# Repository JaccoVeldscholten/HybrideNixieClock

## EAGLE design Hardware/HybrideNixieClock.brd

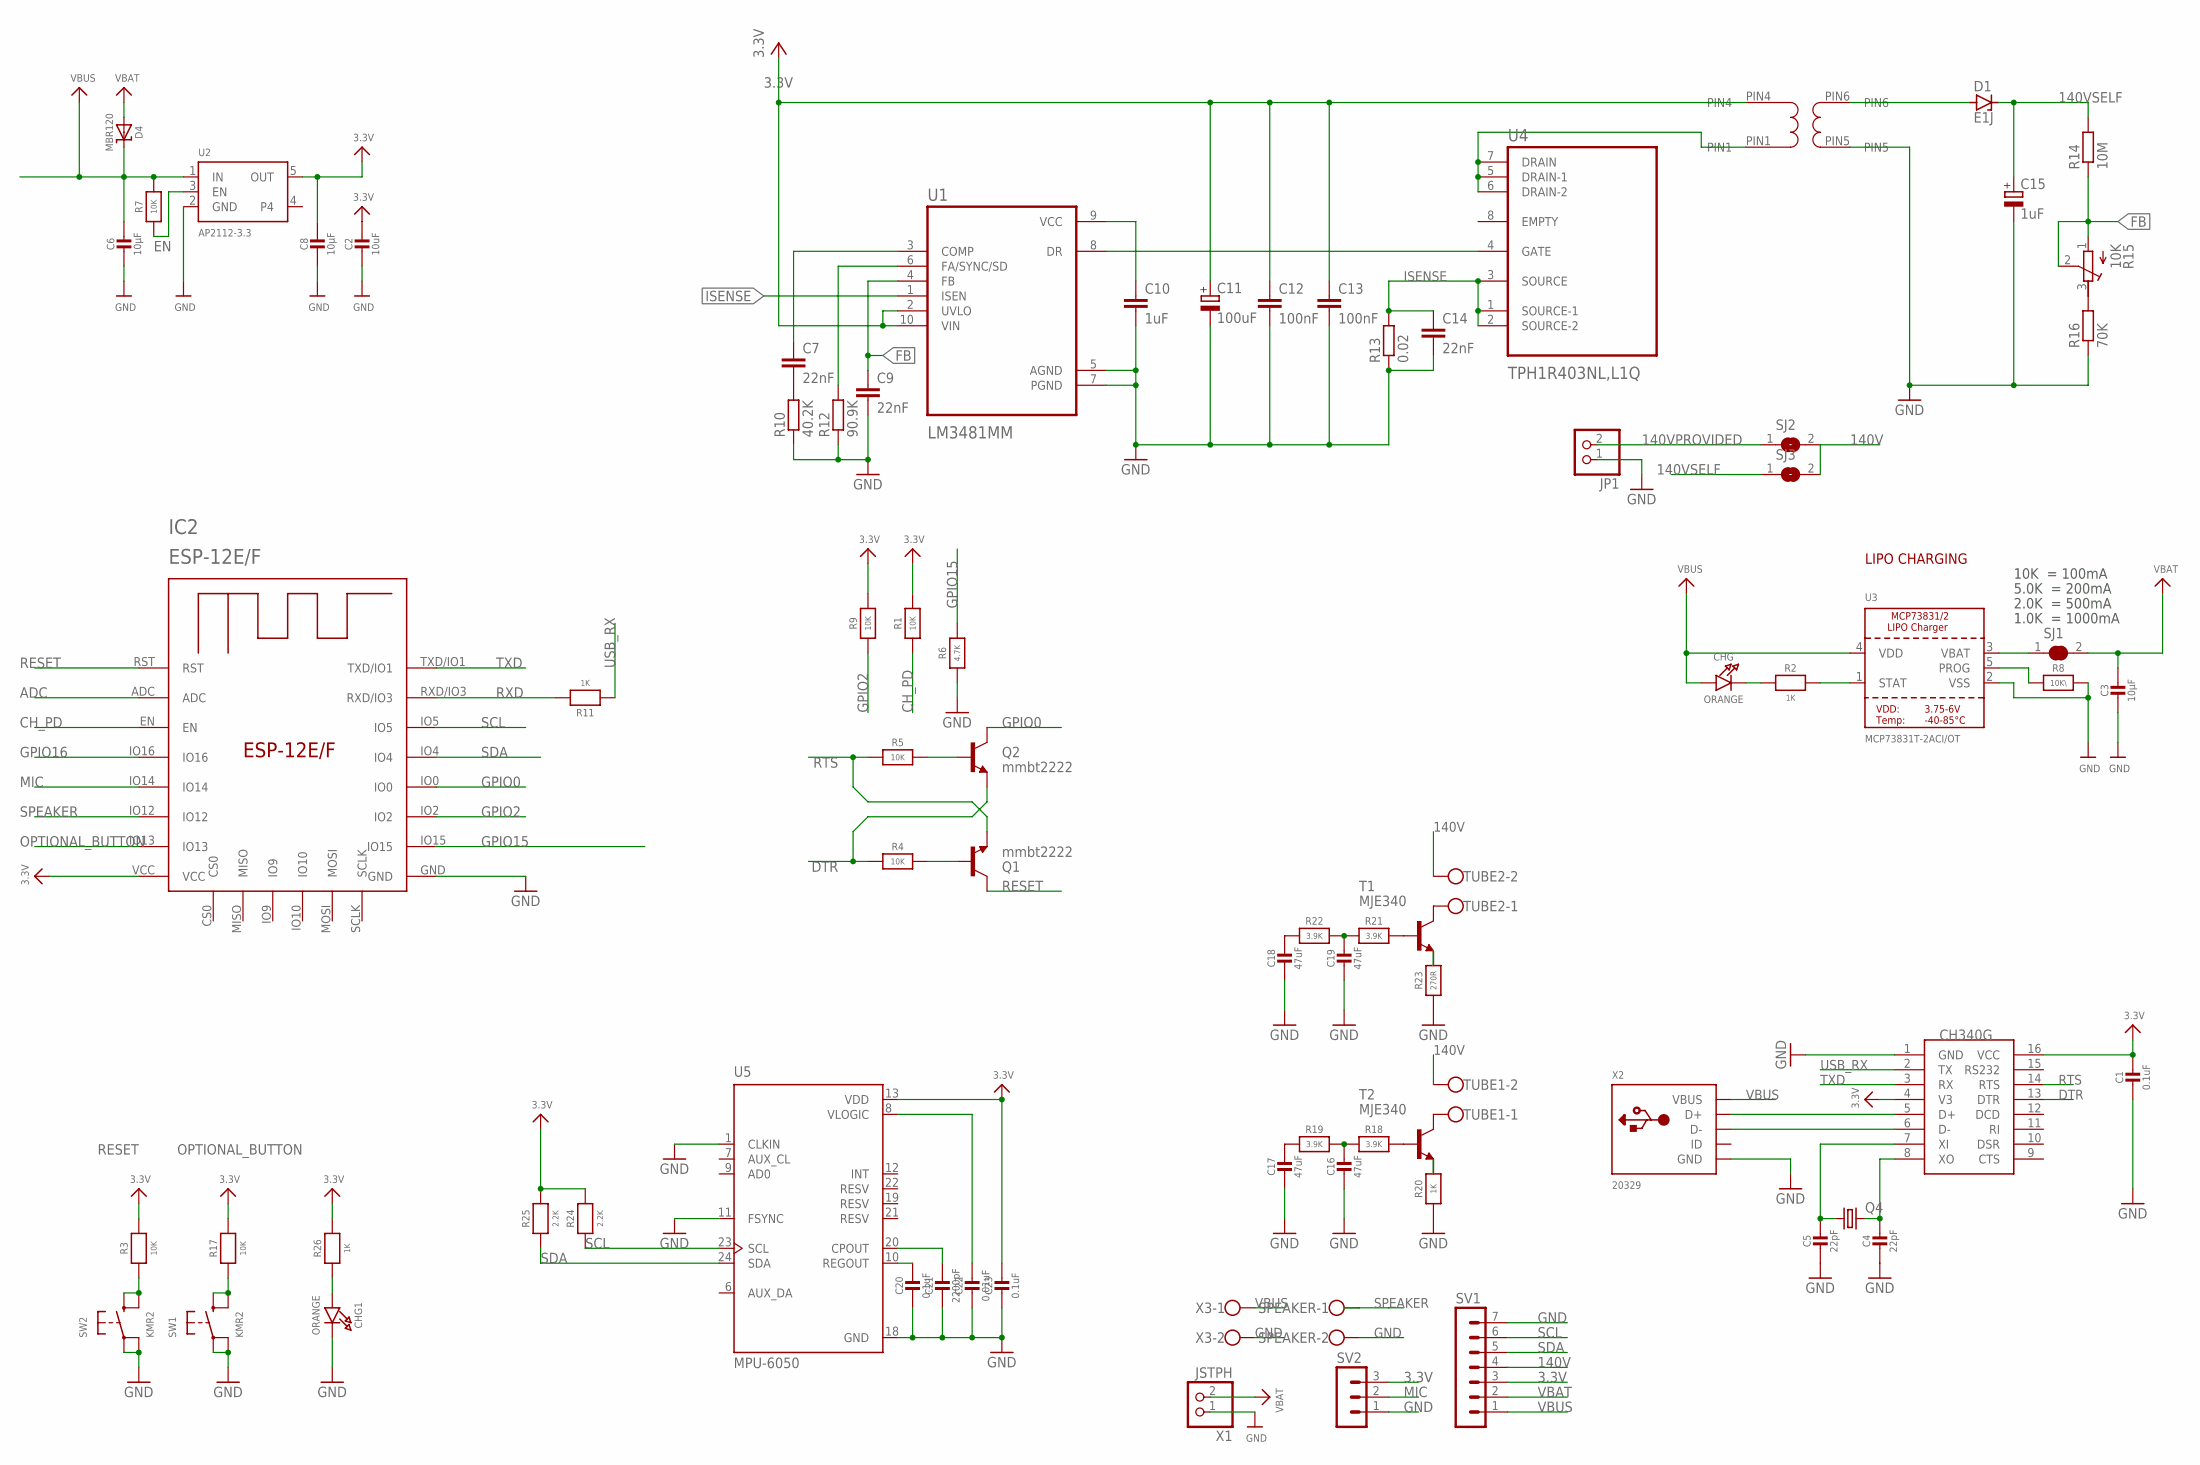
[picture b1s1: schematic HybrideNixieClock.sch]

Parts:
C1, C20, C23: 0.1uF; 0603-NO
C2: 10uF; 0805-NO
C3, C6, C8: 10µF; 0805-NO
C4, C5: 22pF; 0603-NO
C7, C9, C14: 22nF; C0603
C10: 1uF; C0603
C11: 100uF; CT3216
C12, C13: 100nF; C0603
C15: 1uF; CT3216
C16, C17, C18, C19: 47uF; 0603-NO
C21: 2200pF; 0603-NO
C22: 0.01uF; 0603-NO
CHG, CHG1: ORANGE; CHIPLED_0805_NOOUTLINE
D1: E1J; SMB
D4: MBR120; SOD-123
IC2: ESP-12E/F; ESP-12E
JP1: PINHD-1X2; 1X02
Q1, Q2: mmbt2222; SOT23-3
Q4: CRYSTALCTS406; CTS406
R1, R3, R4, R5, R7, R9, R17: 10K; 0603-NO
R2, R20, R26: 1K; 0603-NO
R6: 4.7K; 0603-NO
R8: 10K\; 0603-NO
R10: 40.2K; R0603
R11: 1K; _0603MP
R12: 90.9K; R0603
R13: 0.02; R0603
R14: 10M; R0603
R15: 10K; RTRIM4G/J
R16: 70K; R0603
R18, R19, R21, R22: 3.9K; 0603-NO
R23: 270R; 0603-NO
R24, R25: 2.2K; 0603-NO
SJ1: SOLDERJUMPER_CLOSED; SOLDERJUMPER_CLOSEDWIRE
SJ2, SJ3: SJ
SPEAKER: W237-102
SV1: MA07-1
SV2: MA03-1
SW1, SW2: KMR2; BTN_KMR2_4.6X2.8
T1, T2: MJE340; TO126
TUBE1, TUBE2: W237-102
U1: LM3481MM; SOP50P490X110-10N
U2: AP2112-3.3; SOT23-5
U3: MCP73831T-2ACI/OT; SOT23-5
U4: TPH1R403NL,L1Q; TRANS_TPHR8504PL,L1Q
U5: MPU-6050; QFN50P400X400X95-24N
U$6: TTRN-060S-013
U$7: CH340G; SOIC16
X1: JSTPH; JSTPH2
X2: 20329; 4UCONN_20329_V2
X3: W237-102

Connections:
3.3V: C1.1, C2.1, C8.1, C11.+, C12.1, C13.1, C23.1, IC2.VCC, R1.2, R3.2, R9.2, R17.2, R24.2, R25.2, R26.2, SV1.3, SV2.3, U1.2 (UVLO), U1.10 (VIN), U2.5 (OUT), U5.13 (VDD), U$6.PIN4, U$7.4 (V3), U$7.16 (VCC)
140V: SJ2.2, SJ3.2, SV1.4, TUBE1.2, TUBE2.2
140VPROVIDED: JP1.2, SJ2.1
140VSELF: C15.+, D1.C, R14.2, SJ3.1
ADC: IC2.ADC
CH_PD: IC2.EN, R1.1
DTR: Q2.2 (E), R4.1, U$7.13 (DTR)
EN: R7.1, U2.3 (EN)
FB: C9.1, R14.1, R15.1 (A), R15.2 (S), U1.4 (FB)
GND: C1.2, C2.2, C3.2, C4.2, C5.2, C6.2, C8.2, C9.2, C10.2, C11.-, C12.2, C13.2, C14.2, C15.-, C16.2, C17.2, C18.2, C19.2, C20.2, C21.2, C22.2, C23.2, CHG1.C, IC2.GND, JP1.1, R6.1, R8.2, R10.1, R12.1, R13.1, R16.1, R20.1, R23.1, SPEAKER.2, SV1.7, SV2.1, SW1.A, SW1.A' (P1), SW2.A, SW2.A' (P1), U1.5 (AGND), U1.7 (PGND), U2.2 (GND), U3.2 (VSS), U5.1 (CLKIN), U5.11 (FSYNC), U5.18 (GND), U$6.PIN5, U$7.1 (GND), X1.1, X2.BASE@1 (GND), X2.BASE@2 (GND), X2.GND, X2.SPRT@1 (GND), X2.SPRT@2 (GND), X2.SPRT@3 (GND), X2.SPRT@4 (GND), X3.2
GPIO0: IC2.IO0, Q2.3 (C)
GPIO2: IC2.IO2, R9.1
GPIO15: IC2.IO15, R6.2
GPIO16: IC2.IO16
ISENSE: C14.1, R13.2, U1.1 (ISEN), U4.1 (SOURCE-1), U4.2 (SOURCE-2), U4.3 (SOURCE)
MIC: IC2.IO14, SV2.2
unnamed: CHG.C, R2.1
unnamed: C7.2, R10.2
unnamed: R2.2, U3.1 (STAT)
unnamed: R8.1, U3.5 (PROG)
unnamed: C7.1, U1.3 (COMP)
unnamed: U4.5 (DRAIN-1), U4.6 (DRAIN-2), U4.7 (DRAIN), U$6.PIN1
unnamed: SJ1.1, U3.3 (VBAT)
unnamed: R18.2, T2.3 (B)
unnamed: U$7.6 (D-), X2.D-
unnamed: U$7.5 (D+), X2.D+
unnamed: D1.A, U1.8 (DR), U4.4 (GATE), U$6.PIN6
unnamed: Q1.1 (B), R4.2
unnamed: Q2.1 (B), R5.2
unnamed: C5.1, Q4.1, U$7.7 (XI)
unnamed: C4.1, Q4.3 (2), U$7.8 (XO)
unnamed: C10.1, U1.9 (VCC)
unnamed: R12.2, U1.6 (FA/SYNC/SD)
unnamed: R23.2, T1.1 (E)
unnamed: R15.3 (E), R16.2
unnamed: C16.1, R18.1, R19.2
unnamed: C17.1, R19.1
unnamed: R21.2, T1.3 (B)
unnamed: C19.1, R21.1, R22.2
unnamed: C18.1, R22.1
unnamed: T2.2 (C), TUBE1.1
unnamed: T1.2 (C), TUBE2.1
unnamed: R20.2, T2.1 (E)
unnamed: C20.1, U5.10 (REGOUT)
unnamed: C21.1, U5.20 (CPOUT)
unnamed: CHG1.A, R26.1
unnamed: C22.1, U5.8 (VLOGIC)
OPTIONAL_BUTTON: IC2.IO13, R17.1, SW1.B (S), SW1.B' (S1)
RESET: IC2.RST, Q1.3 (C), R3.1, SW2.B (S), SW2.B' (S1)
RTS: Q1.2 (E), R5.1, U$7.14 (RTS)
RXD: IC2.RXD/IO3, R11.2
SCL: IC2.IO5, R24.1, SV1.6, U5.23 (SCL)
SDA: IC2.IO4, R25.1, SV1.5, U5.24 (SDA)
SPEAKER: IC2.IO12, SPEAKER.1
TXD: IC2.TXD/IO1, U$7.3 (RX)
USB_RX: R11.1, U$7.2 (TX)
VBAT: C3.1, D4.A, SJ1.2, SV1.2, X1.2
VBUS: C6.1, CHG.A, D4.C, R7.2, SV1.1, U2.1 (IN), U3.4 (VDD), X2.VBUS, X3.1

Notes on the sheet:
10K = 100mA
5.0K = 200mA
2.0K = 500mA
1.0K = 1000mA
LIPO CHARGING

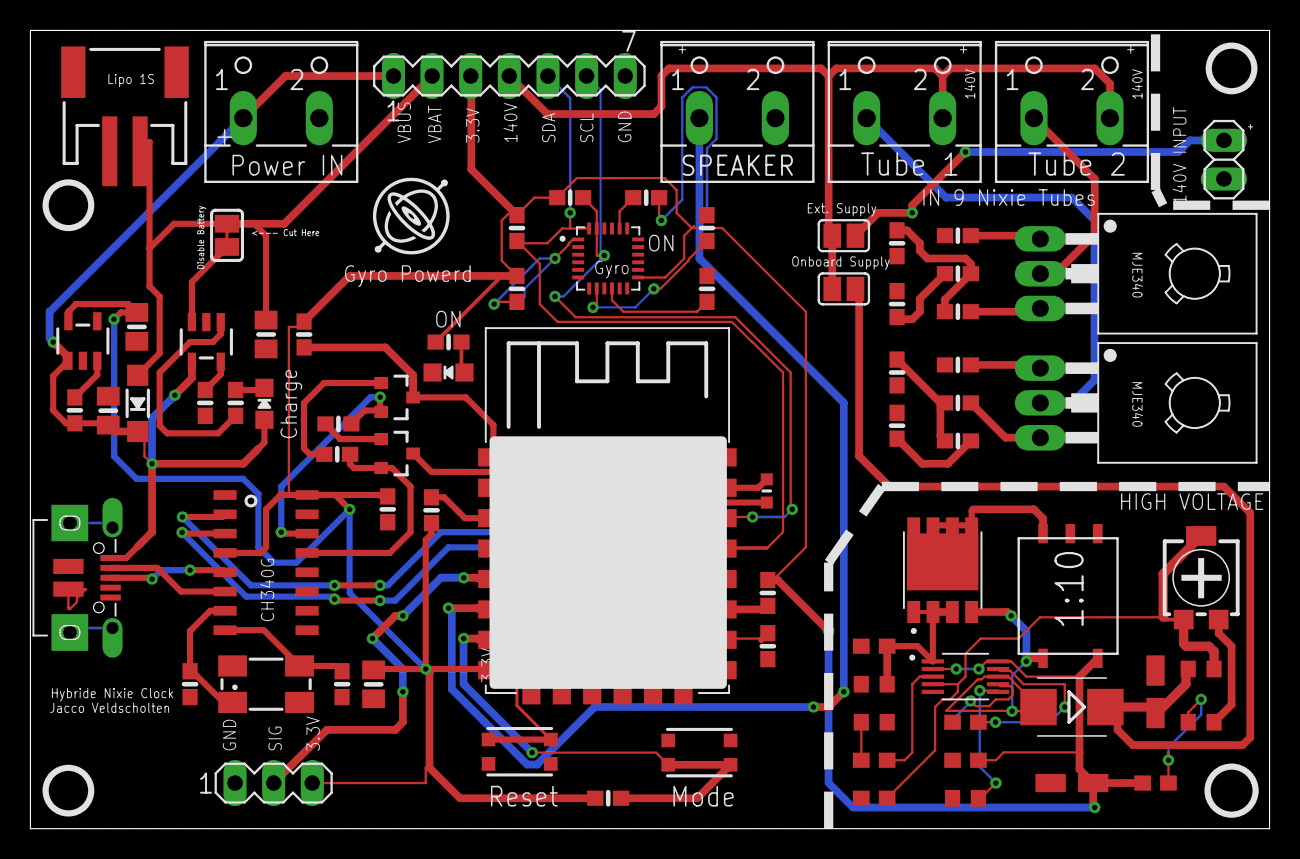
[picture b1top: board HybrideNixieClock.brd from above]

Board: 2 copper layers, 81.5 x 52.5 mm, 80 parts (0 on the bottom side), 56 nets.

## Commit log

2020-09-21 Added Schematic
2020-09-21 Create Schematic
2020-09-21 Moved Hardware to Folder
2020-09-22 Final V1 Hardware
2020-10-19 Updated Hardware V2
2020-12-07 Initial Master
2020-12-07 First setup. Connecting WifiManager + TimeManager
    First steps taken
    - Setting up UDP time
    - Working Gyro
    - Working WiFi Manager
    ToDo: Working Web Page to config the clock
2020-12-27 Initial Release webpage

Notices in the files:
parts and their libraries:
microbuilder: This work is placed in the public domain, and may be freely used for commercial and non-commercial work with the following conditions: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
SparkFun: Licensing: CC v3.0 Share-Alike You are welcome to use this library for commercial purposes.
